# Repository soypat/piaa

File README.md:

# piaa
PIAA, inspired by the [CIAA project](https://github.com/ciaa/Hardware).

The PIAA is a open source [printed cicuit board](https://en.wikipedia.org/wiki/Printed_circuit_board) design for use in industrial settings where [electromagnetic interference](https://en.wikipedia.org/wiki/Electromagnetic_interference) is of great concern. The on board processor is intended to be the RP2040 contained in the [Raspberry Pi Pico](https://www.raspberrypi.com/products/raspberry-pi-pico/) package

Features:
- All I/O except for GPIO header come with extensive EMI protection.
- Wide temperature range components.
- 1 RS485 peripheral using MAX3072E.
- 6 Digital outputs with PWM capabilities.
- 4 digital inputs.
- Powered be 6-24V input.
- 8 additional GPIO on header with SPI, I2C, UART, PWM, PIO capabilities. This header is connected to GPIO0 through GPIO7.
- Regulated 3.3V and 5V outputs.
- Grounded padding on sides of Proant wifi/bluetooth antenna to potentially increase antenna gain (not tested).

# Kicad: Project setup
This project was made entirely with Kicad.

Download external dependencies with:

```sh
git submodule update --init
```

## Further setup
I'd believe the project should be set automatically since I've taken care to include all libraries as "Project" libraries, not "Global". 
In any case, if that fails you may follow the steps detailed here to setup any symbol, footprint and 3D model libraries that may be needed
to work or visualize the PIAA.

1. After initializing git submodules with external symbol and footprint libraries (with `git submodule update --init`) follow the symbol installation instructions at [this link](https://github.com/ncarandini/KiCad-RP-Pico/blob/main/Install%20instructions.md) and use the footprint in the folder [RP-Pico Libraries](./submodules/KiCad-RP-Pico/RP-Pico Libraries).

2. Setup `piaalib` symbol and footprint libraries. They are located under [design/lib/piaalib](./design/lib/piaalib).
The steps to adding these libraries are the same as with the RP-Pico libraries.

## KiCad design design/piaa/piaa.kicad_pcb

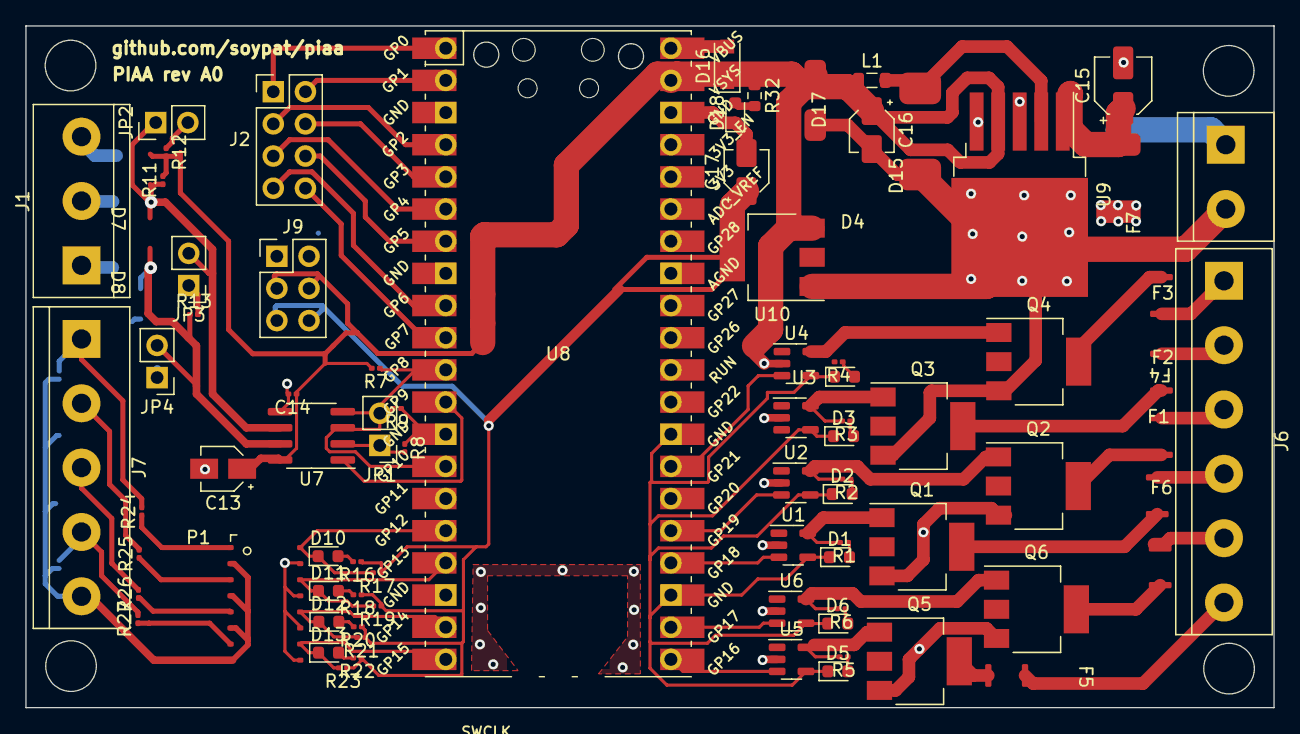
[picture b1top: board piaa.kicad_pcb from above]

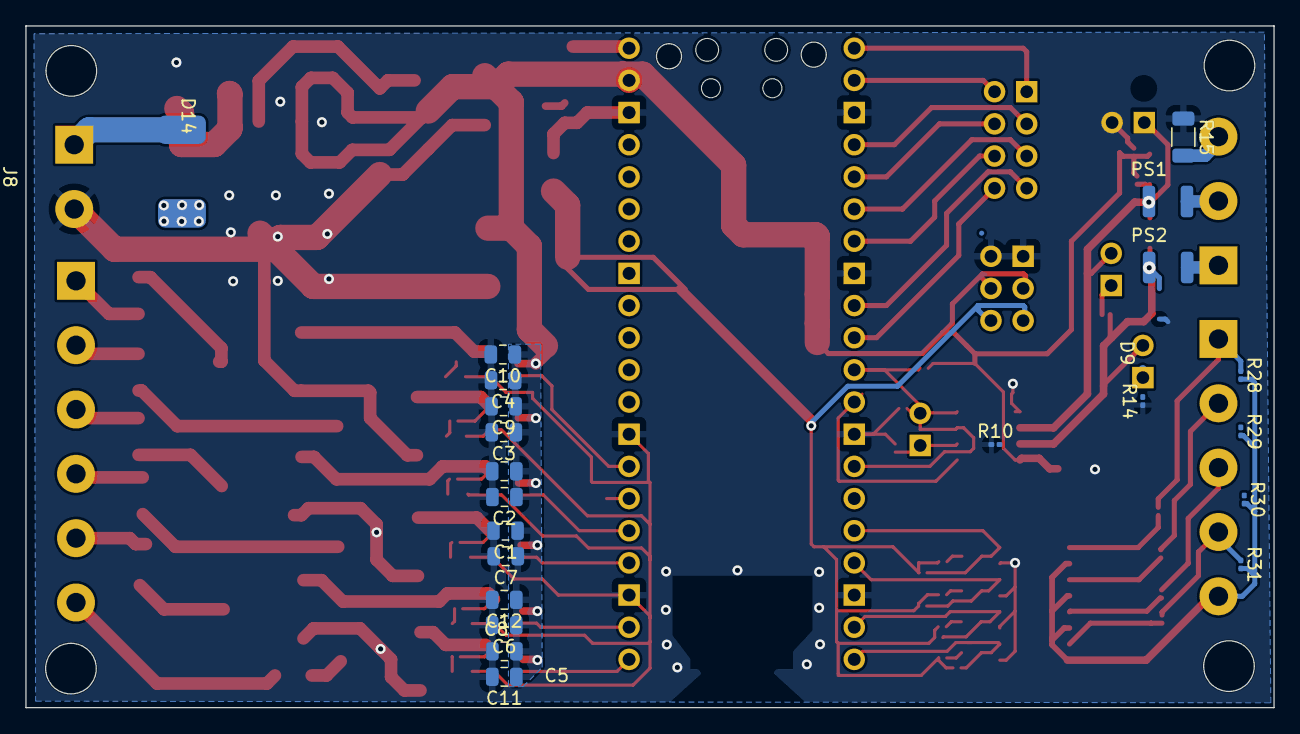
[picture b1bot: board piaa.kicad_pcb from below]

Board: 2 copper layers, 98.6 x 53.8 mm, 104 parts (23 on the bottom side), 76 nets.

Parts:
C1, C2, C3, C4, C5, C6: 1uF; C_0805_2012Metric
C7, C8, C9, C10, C11, C12: 100nF; C_0805_2012Metric
C13: 10uF/6V3; CP_Elec_3x5.3
C14: 100nF; C_0201_0603Metric
C15: 470uF; CP_Elec_4x3
C16: 330uF; CP_Elec_3x5.4
C17: 10uF; CP_Elec_3x5.4
D1, D2, D3, D4, D5, D6, D18: LED RED; LED_0603_1608Metric
D7, D8, D9: PSD12C; SOD-323
D10, D11, D12, D13: LED YL; LED_0603_1608Metric
D14: MURS360T3G
D15: B540C-13-F
D16: PMEG3020EH; D_SOD-123F
D17: SMAZ5V6
F1, F2, F3, F4, F5, F6: PTS12066V100
F7: PTS18126V300
J1: Screw_Terminal_01x03; TerminalBlock_bornier-3_P5.08mm
J2: Conn_02x04_Counter_Clockwise; PinHeader_2x04_P2.54mm_Vertical
J6: Screw_Terminal_01x06; TerminalBlock_bornier-6_P5.08mm
J7: Screw_Terminal_01x05; TerminalBlock_bornier-5_P5.08mm
J8: Screw_Terminal_01x02; TerminalBlock_bornier-2_P5.08mm
J9: Conn_01x06_Female; PinHeader_2x03_P2.54mm_Vertical
JP1, JP2, JP3, JP4: jumper; PinHeader_1x02_P2.54mm_Vertical
L1: 47uH; L_0805_2012Metric
P1: PS2805-4; SSOP-16_0.5x0.4mm_pitch1.27mm
PS1, PS2: USMF020
Q1, Q2, Q3, Q4, Q5, Q6: FQT13N06L; SOT-223
R1, R2, R3, R4, R5, R6: 330; R_0201_0603Metric
R7, R8, R9: 4k7; R_0201_0603Metric
R10, R11, R17, R19, R21, R23: 100k; R_0201_0603Metric
R12, R14: 680; R_0201_0603Metric
R13: 120; R_0201_0603Metric
R15: 100 @ 1/2W; R_1206_3216Metric
R16, R18, R20, R22: 2.2k; R_0201_0603Metric
R24, R25, R26, R27: 3.3k; R_0201_0603Metric
R28, R29, R30, R31: 4.7k; R_0201_0603Metric
R32: 1k; R_0603_1608Metric
U1, U2, U3, U4, U5, U6: MCP1416; SOT-23-5
U7: MAX3072E; SOIC-8_3.9x4.9mm_P1.27mm
U8: Pico; RPi_Pico_SMD_TH
U9: LM2596S-5; TO-263-5_TabPin3
U10: NCP1117-3.3_SOT223; SOT-223-3_TabPin2

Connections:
+3V3: C17.1, J9.5, J9.6, R16.1, R17.1, R18.1, R19.1, R20.1, R21.1, R22.1, R23.1, U10.2 (VO)
+5V: C1.1, C2.1, C3.1, C4.1, C5.1, C6.1, C7.1, C8.1, C9.1, C10.1, C11.1, C12.1, C13.1, C14.1, C16.1, D7.1, D16.1 (K), D17.2, J9.3, J9.4, L1.1, R7.2, R11.2, R12.2, R32.1, U1.2 (Vdd), U2.2 (Vdd), U3.2 (Vdd), U4.2 (Vdd), U5.2 (Vdd), U6.2 (Vdd), U7.8 (VCC), U8.39 (VSYS), U9.4 (FB), U10.3 (VI)
+24V: D14.1, J8.1
/COM: J7.5, P1.2 (CA0), P1.4 (CA1), P1.6 (CA2), P1.8 (CA3), R28.2, R29.2, R30.2, R31.2
/DIN0: D10.1 (K), P1.16 (C0), R17.2, U8.16 (GPIO12)
/DIN1: D11.1 (K), P1.14 (C1), R19.2, U8.17 (GPIO13)
/DIN2: D12.1 (K), P1.12 (C2), R21.2, U8.19 (GPIO14)
/DIN3: D13.1 (K), P1.10 (C3), R23.2, U8.20 (GPIO15)
/DOUT0: U5.3 (IN), U8.21 (GPIO16)
/DOUT1: U6.3 (IN), U8.22 (GPIO17)
/DOUT2: U1.3 (IN), U8.24 (GPIO18)
/DOUT3: U2.3 (IN), U8.25 (GPIO19)
/DOUT4: U3.3 (IN), U8.26 (GPIO20)
/DOUT5: U4.3 (IN), U8.27 (GPIO21)
/GPIO0: J2.1, U8.1 (GPIO0)
/GPIO1: J2.2, U8.2 (GPIO1)
/GPIO2: J2.3, U8.4 (GPIO2)
/GPIO3: J2.4, U8.5 (GPIO3)
/GPIO4: J2.5, U8.6 (GPIO4)
/GPIO5: J2.6, U8.7 (GPIO5)
/GPIO6: J2.7, U8.9 (GPIO6)
/GPIO7: J2.8, U8.10 (GPIO7)
/IN0: J7.1, R24.2, R28.1
/IN1: J7.2, R25.2, R29.1
/IN2: J7.3, R26.2, R30.1
/IN3: J7.4, R27.2, R31.1
/OUT0: F5.1, J6.6
/OUT1: F6.1, J6.5
/OUT2: F1.1, J6.4
/OUT3: F2.1, J6.3
/OUT4: F3.1, J6.2
/OUT5: F4.1, J6.1
/RS485_DIR: JP1.2 (B), R9.2, U7.3 (DE), U8.14 (GPIO10)
/RS485_RX: U7.1 (RO), U8.12 (GPIO9)
/RS485_TX: R7.1, U7.4 (DI), U8.11 (GPIO8)
GND: C1.2, C2.2, C3.2, C4.2, C5.2, C6.2, C7.2, C8.2, C9.2, C10.2, C11.2, C12.2, C13.2, C14.2, C15.2, C16.2, C17.2, D1.1 (K), D2.1 (K), D3.1 (K), D4.1 (K), D5.1 (K), D6.1 (K), D9.2, D15.1, D17.1, D18.1 (K), J8.2, J9.1, J9.2, P1.9 (E3), P1.11 (E2), P1.13 (E1), P1.15 (E0), Q1.3 (S), Q2.3 (S), Q3.3 (S), Q4.3 (S), Q5.3 (S), Q6.3 (S), R8.1, R9.1, R10.1, R14.1, R15.1, U1.4 (GND), U2.4 (GND), U3.4 (GND), U4.4 (GND), U5.4 (GND), U6.4 (GND), U7.5 (GND), U8.3 (GND), U8.8 (GND), U8.13 (GND), U8.18 (GND), U8.23 (GND), U8.28 (GND), U8.38 (GND), U9.3 (GND), U9.5 (~ON/OFF), U10.1 (GND)
unnamed: C15.1, F7.2, U9.1 (VIN)
unnamed: D1.2 (A), R1.1
unnamed: D2.2 (A), R2.1
unnamed: D3.2 (A), R3.1
unnamed: D4.2 (A), R4.1
unnamed: D5.2 (A), R5.1
unnamed: D6.2 (A), R6.1
unnamed: D7.2, D8.1, JP2.1 (A), JP3.2 (B), PS1.1, R11.1, U7.6 (A)
unnamed: D8.2, D9.1, JP4.2 (B), PS2.1, R10.2, R13.1, U7.7 (B)
unnamed: D10.2 (A), R16.2
unnamed: D11.2 (A), R18.2
unnamed: D12.2 (A), R20.2
unnamed: D13.2 (A), R22.2
unnamed: D14.2, F7.1
unnamed: D15.2, L1.2, U9.2 (OUT)
unnamed: D18.2 (A), R32.2
unnamed: F1.2, Q1.4 (D)
unnamed: F2.2, Q2.4 (D)
unnamed: F3.2, Q3.4 (D)
unnamed: F4.2, Q4.4 (D)
unnamed: F5.2, Q5.4 (D)
unnamed: F6.2, Q6.4 (D)
unnamed: J1.3, R15.2
unnamed: JP1.1 (A), R8.2, U7.2 (~RE)
unnamed: JP2.2 (B), R12.1
unnamed: JP3.1 (A), R13.2
unnamed: JP4.1 (A), R14.2
unnamed: P1.1 (AC0), R24.1
unnamed: P1.3 (AC1), R25.1
unnamed: P1.5 (AC2), R26.1
unnamed: P1.7 (AC3), R27.1
unnamed: J1.2, PS1.2
unnamed: J1.1, PS2.2
unnamed: Q1.1 (G), R1.2, U1.5 (OUT)
unnamed: Q2.1 (G), R2.2, U2.5 (OUT)
unnamed: Q3.1 (G), R3.2, U3.5 (OUT)
unnamed: Q4.1 (G), R4.2, U4.5 (OUT)
unnamed: Q5.1 (G), R5.2, U5.5 (OUT)
unnamed: Q6.1 (G), R6.2, U6.5 (OUT)
VBUS: D16.2 (A), U8.40 (VBUS)

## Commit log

2023-03-05 fix symbols, begin layout
2023-03-05 update to pcb drawing
2023-03-05 finalized drawing
2023-03-05 add antenna keepout and padding
2023-03-05 add rev0.0.0 pdf
2023-03-05 add antenna padding disclaimer
2023-03-05 specify project was made with kicad
2023-03-08 updates to schematic
2023-03-08 better setup instructions
2023-03-09 fix header and bornier size
2023-03-09 thicker 3v3 line
